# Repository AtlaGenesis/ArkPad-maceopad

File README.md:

# ArkPad-maceopad
A Hackpad project for Hack Club's Blueprint

It has 10 keys, each are different shortcuts that makes you do things on you computer easier!

## PCB
[PCB Here](./ArkPad%20KiCad%20Project%20files/ArkPad%201.kicad_pcb):

## Scematics:
[Sch Here](./ArkPad%20KiCad%20Project%20files/ArkPad%201.kicad_sch)

## Case:
I design it using Blender, I'm more used to it, and I made it faster in Blender, Fusion confuses me, and Blender has more features, and much easier to use, I also have much more experience on Blender than on Fusion, it can also be as precise.[Case Here](./ArkPad/ArkPad%20case)

## Firmware
I used KMK for the firmware, it's in the [ArkPad Firmware files](./ArkPad/Arkpad%20Firmware)

## [BOM](./ArkPad/BOM.md)
- 1x Seed Xiao RP2040 DIP
- 10x Cherry MX 1.00u
- 2x LED SK6812 MINI
- 3D printed Case (ArkPad Base & ArkPad top)
- 4x 3.4mm fastening screws

All the files are inside the ArkPad folder!

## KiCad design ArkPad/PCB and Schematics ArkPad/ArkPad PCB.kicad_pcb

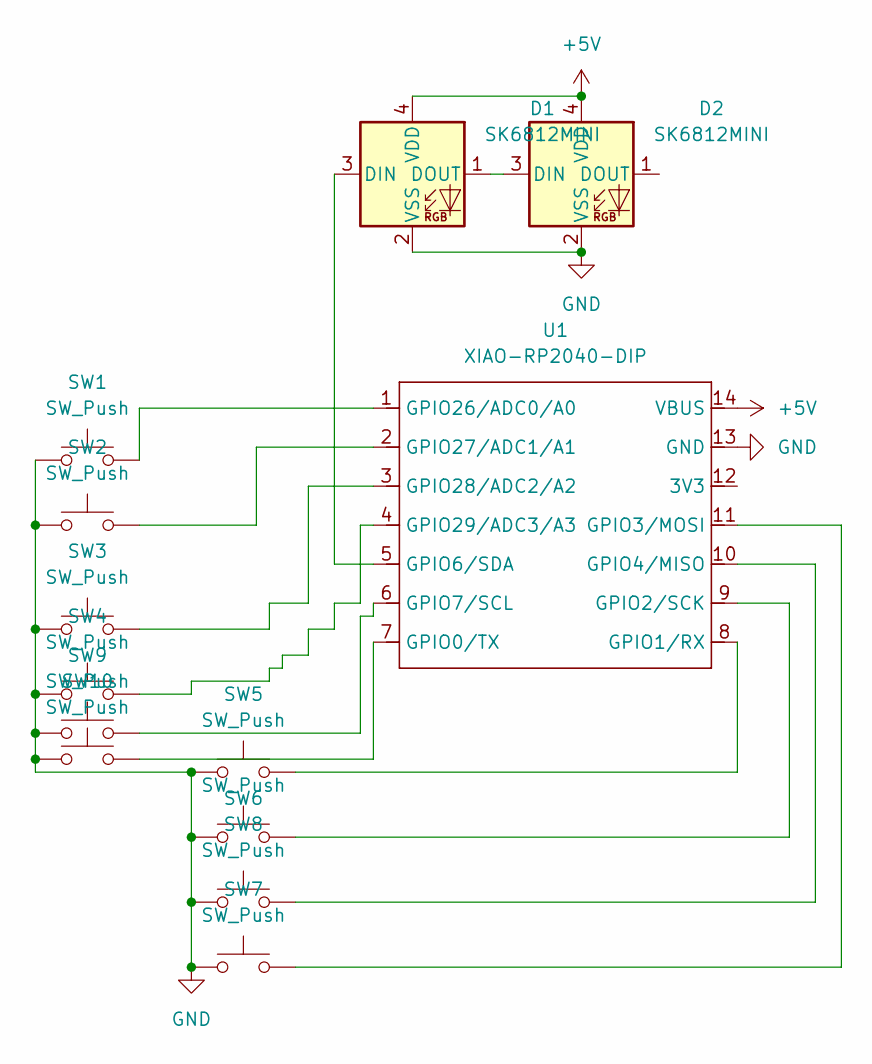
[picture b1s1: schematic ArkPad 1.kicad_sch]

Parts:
D1, D2: SK6812MINI; LED_SK6812MINI_PLCC4_3.5x3.5mm_P1.75mm
SW1, SW2, SW3, SW4, SW5, SW6, SW7, SW8, SW9, SW10: SW_Push; SW_Cherry_MX_1.00u_PCB
U1: XIAO-RP2040-DIP

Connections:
+3V3: U1.12 (3V3)
+5V: D1.4 (VDD), D2.4 (VDD), U1.14 (VBUS)
GND: D1.2 (VSS), D2.1 (DOUT), D2.2 (VSS), SW1.1, SW2.1, SW3.1, SW4.1, SW5.1, SW6.1, SW7.1, SW8.1, SW9.1, SW10.1, U1.13 (GND)
unnamed: D1.3 (DIN), U1.5 (GPIO6/SDA)
unnamed: D1.1 (DOUT), D2.3 (DIN)
unnamed: SW10.2, U1.7 (GPIO0/TX)
unnamed: SW5.2, U1.8 (GPIO1/RX)
unnamed: SW6.2, U1.9 (GPIO2/SCK)
unnamed: SW7.2, U1.11 (GPIO3/MOSI)
unnamed: SW8.2, U1.10 (GPIO4/MISO)
unnamed: SW9.2, U1.6 (GPIO7/SCL)
unnamed: SW1.2, U1.1 (GPIO26/ADC0/A0)
unnamed: SW2.2, U1.2 (GPIO27/ADC1/A1)
unnamed: SW3.2, U1.3 (GPIO28/ADC2/A2)
unnamed: SW4.2, U1.4 (GPIO29/ADC3/A3)

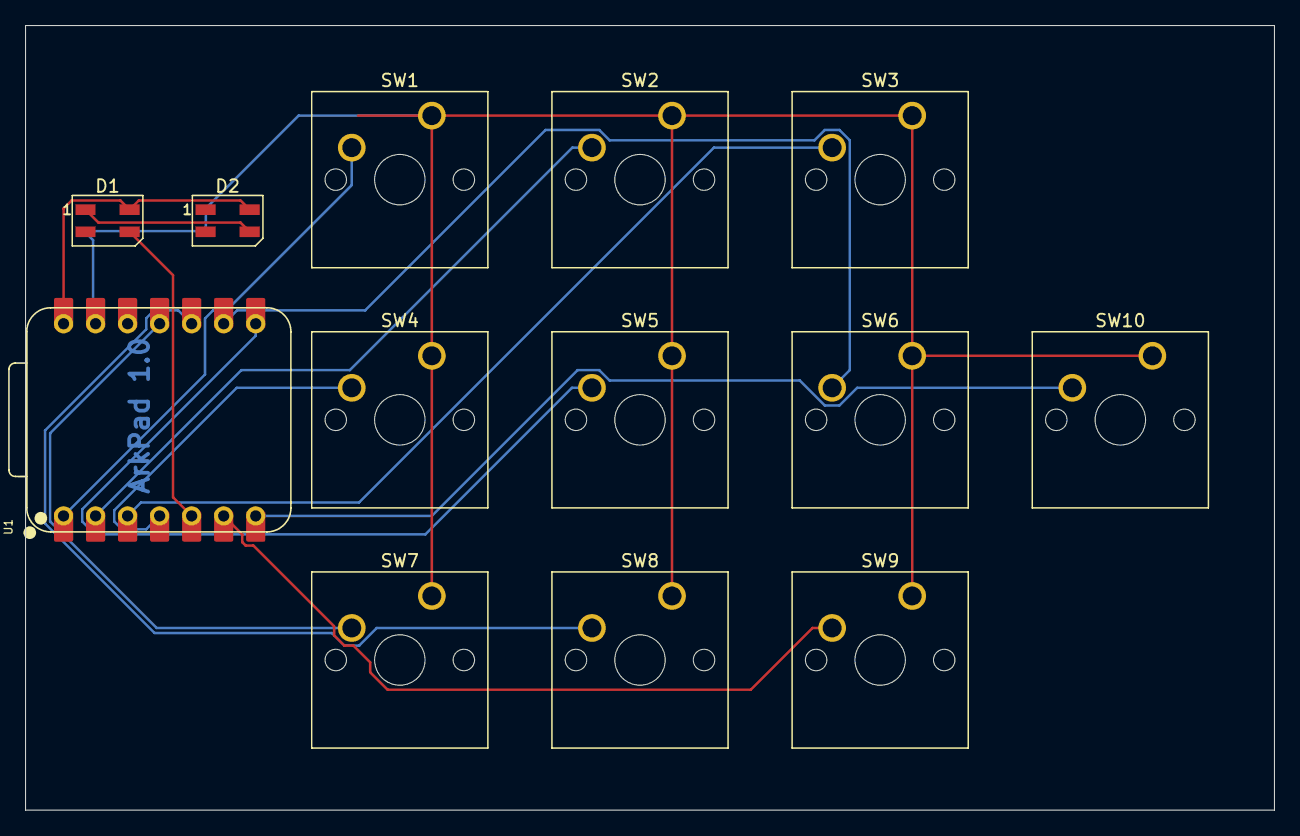
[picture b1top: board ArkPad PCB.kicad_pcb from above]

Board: 2 copper layers, 99.1 x 62.2 mm, 13 parts (0 on the bottom side), 14 nets.

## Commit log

2026-01-05 changes the Zip into a folder for easier access
2026-01-05 Mention files are inside the ArkPad folder
    Added note about file location in README.
2026-01-06 kicad project file addition
2026-03-28 added the gerber files
2026-03-28 Update PCB section with project file link
    test
2026-03-28 Update README.md
    test 2
2026-03-28 Fix links and enhance README content
    Updated links and added references to PCB, schematics, case, firmware, and BOM sections.
2026-03-30 Fix formatting in BOM.md for better readability
